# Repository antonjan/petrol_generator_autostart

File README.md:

# petrol_generator_autostart
This project is a remote controle generator start and stop system via Telegram web interface. It has 2 opto inputs 2  relay outputs and 2 servo Chocke controlerelay

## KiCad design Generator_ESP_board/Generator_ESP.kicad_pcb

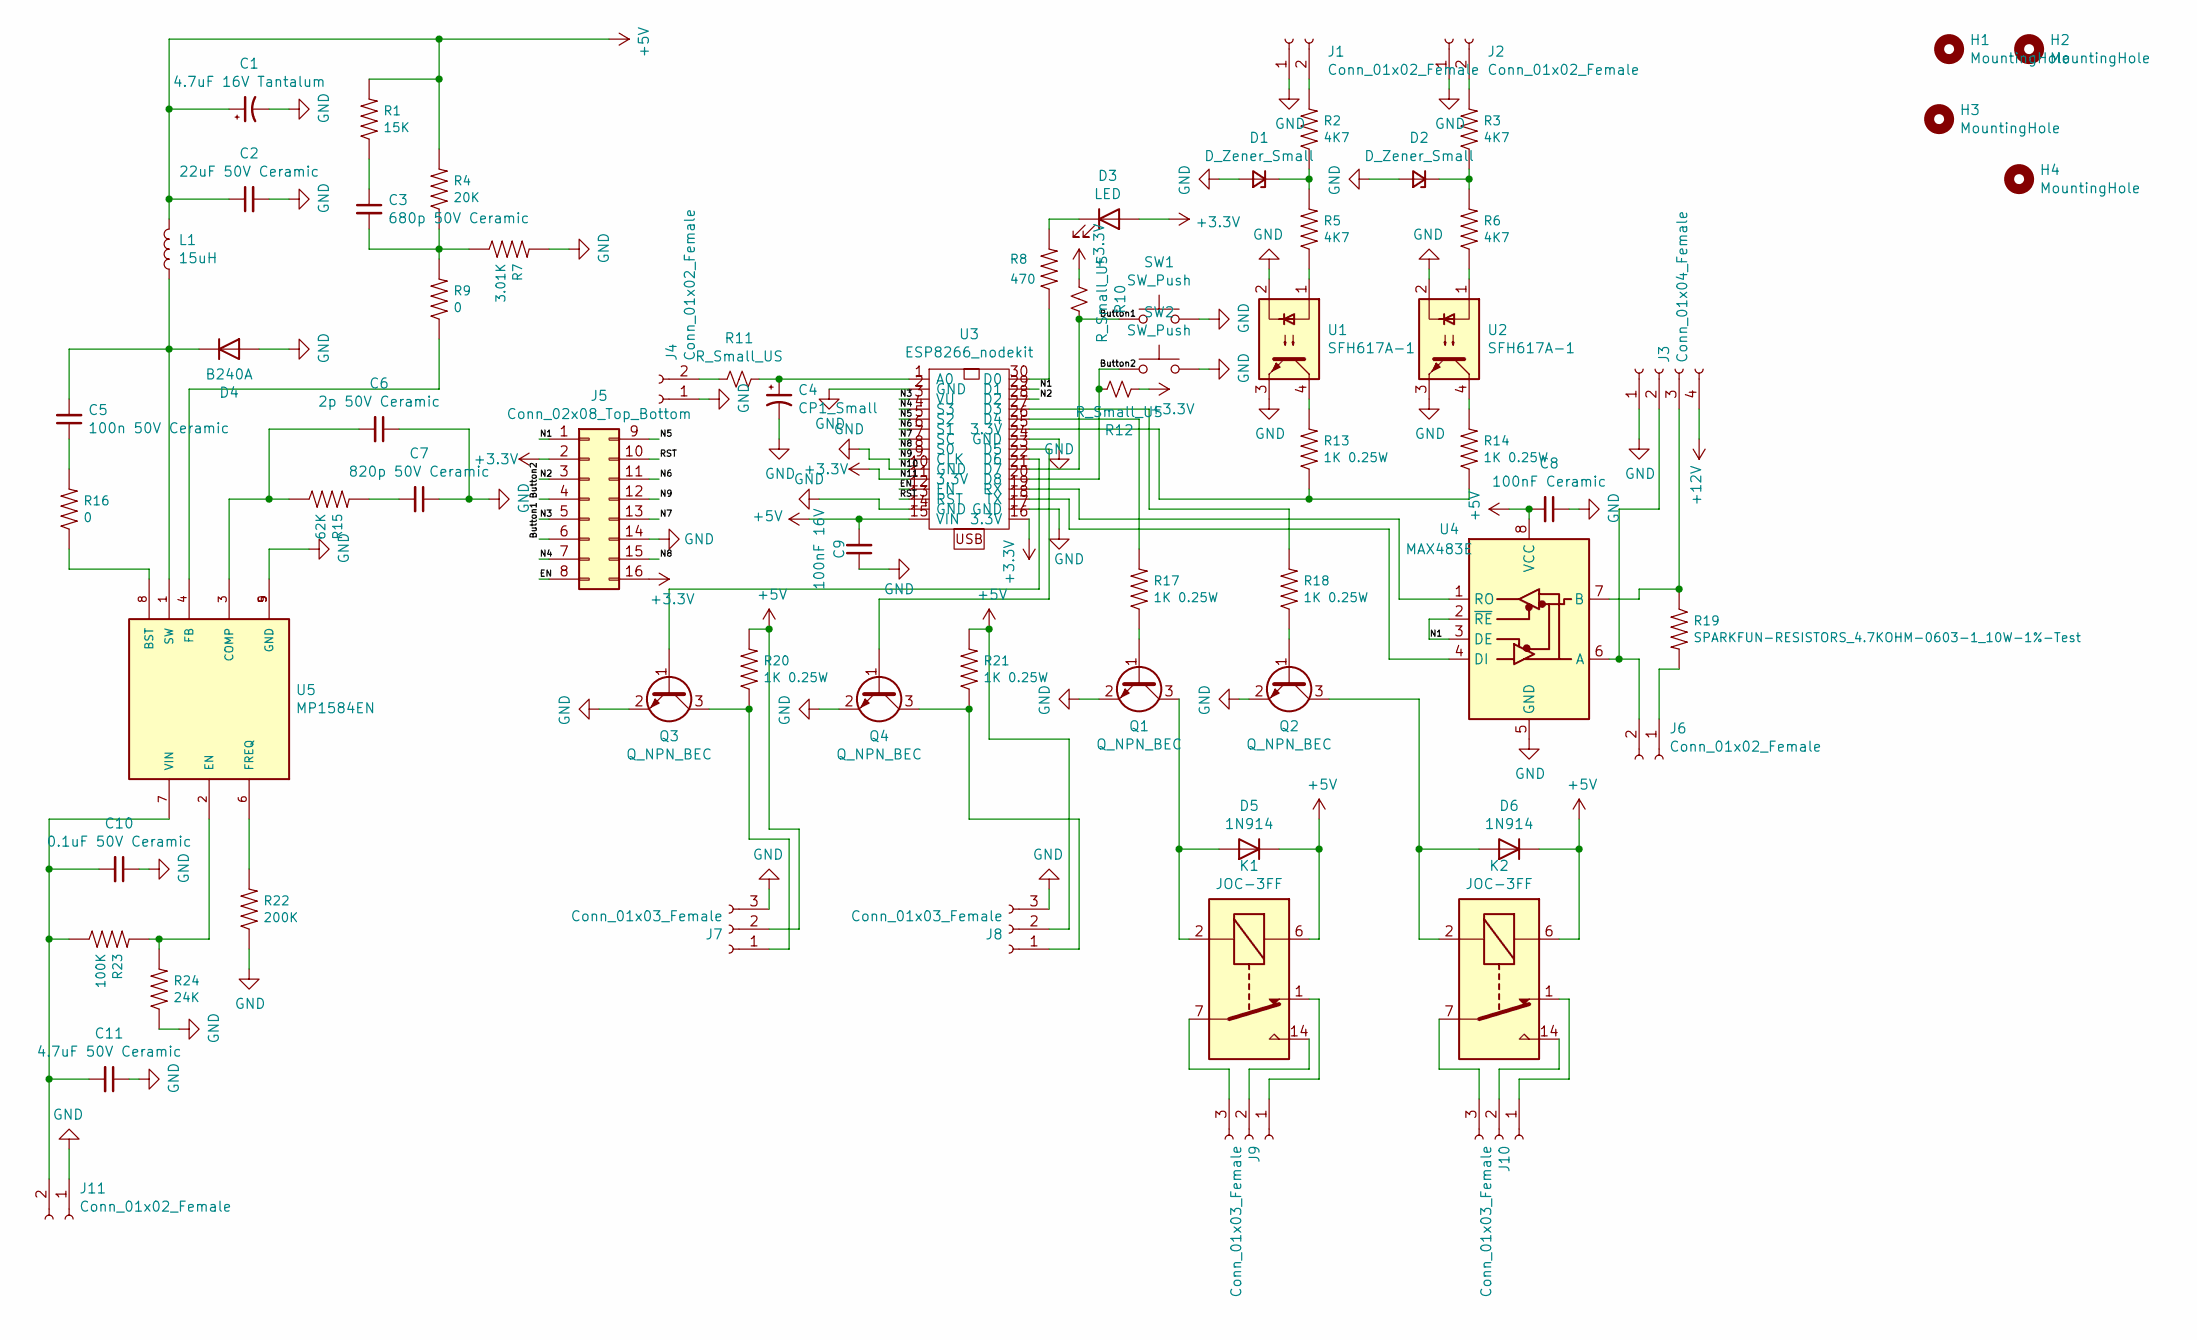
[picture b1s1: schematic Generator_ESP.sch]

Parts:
C1: 4.7uF 16V Tantalum; C_0805_2012Metric
C2: 22uF 50V Ceramic; C_2220_5650Metric
C3: 680p 50V Ceramic; C_0805_2012Metric
C4: CP1_Small; C_0805_2012Metric
C5: 100n 50V Ceramic; C_0805_2012Metric
C6: 2p 50V Ceramic; C_0805_2012Metric
C7: 820p 50V Ceramic; C_0805_2012Metric
C8: 100nF Ceramic; C_0805_2012Metric
C9: 100nF 16V; C_0805_2012Metric
C10: 0.1uF 50V Ceramic; C_0805_2012Metric
C11: 4.7uF 50V Ceramic; C_1206_3216Metric
D1, D2: D_Zener_Small; D_MELF
D3: LED; LED_D3.0mm
D4: B240A; D_SMA
D5, D6: 1N914; D_0805_2012Metric
H1, H2, H3, H4: MountingHole; MountingHole_3.2mm_M3
J1, J2, J11: Conn_01x02_Female; PhoenixContact_MCV_1,5_2-G-5.08_1x02_P5.08mm_Vertical
J3: Conn_01x04_Female; PhoenixContact_MCV_1,5_4-G-5.08_1x04_P5.08mm_Vertical
J4, J6: Conn_01x02_Female; PinHeader_1x02_P2.54mm_Vertical
J5: Conn_02x08_Top_Bottom; PinHeader_2x08_P2.54mm_Vertical
J7, J8, J9, J10: Conn_01x03_Female; PhoenixContact_MCV_1,5_3-G-5.08_1x03_P5.08mm_Vertical
K1, K2: JOC-3FF; Relay_SPDT_Finder_36.11
L1: 15uH; L_12x12mm_H4.5mm
Q1, Q2, Q3, Q4: Q_NPN_BEC; SOT-23
R1: 15K; R_0805_2012Metric_Pad1.20x1.40mm_HandSolder
R2, R3, R5, R6: 4K7; R_0805_2012Metric_Pad1.20x1.40mm_HandSolder
R4: 20K; R_0805_2012Metric_Pad1.20x1.40mm_HandSolder
R7: 3.01K; R_0805_2012Metric_Pad1.20x1.40mm_HandSolder
R8: 470; R_0805_2012Metric_Pad1.20x1.40mm_HandSolder
R9, R16: 0; R_0805_2012Metric_Pad1.20x1.40mm_HandSolder
R10, R11, R12: R_Small_US; R_0805_2012Metric_Pad1.20x1.40mm_HandSolder
R13, R14, R17, R18, R20, R21: 1K 0.25W; R_0805_2012Metric_Pad1.20x1.40mm_HandSolder
R15: 62K; R_0805_2012Metric_Pad1.20x1.40mm_HandSolder
R19: SPARKFUN-RESISTORS_4.7KOHM-0603-1_10W-1%-Test; R_0805_2012Metric_Pad1.20x1.40mm_HandSolder
R22: 200K; R_0805_2012Metric_Pad1.20x1.40mm_HandSolder
R23: 100K; R_0805_2012Metric_Pad1.20x1.40mm_HandSolder
R24: 24K; R_0805_2012Metric_Pad1.20x1.40mm_HandSolder
SW1, SW2: SW_Push; SW_SPST_B3U-1000P
U1, U2: SFH617A-1; SMDIP-4_W7.62mm
U3: ESP8266_nodekit; SEEED_113990105
U4: MAX483E; SOIC127P600X175-8N
U5: MP1584EN; SOIC127P600X170-9N

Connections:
+3V3: D3.2 (A), J5.2, J5.16, R10.2, R12.2, U3.11 (3.3V), U3.16 (3.3V)
+5V: C1.1, C2.1, C8.2, C9.2, D5.1 (K), D6.1 (K), J7.2, J8.2, K1.6, K2.6, L1.2, R1.2, R4.2, R20.2, R21.2, U3.15 (VIN), U4.8 (VCC)
+12V: J3.4
/Button1: J5.6, R10.1, SW1.1, U3.21 (D7)
/Button2: J5.4, R12.1, SW2.1, U3.20 (D8)
/EN: J5.8, U3.12 (EN)
/N1: J5.1, U3.29 (D1), U4.2 (~RE), U4.3 (DE)
/N2: J5.3, U3.28 (D2)
/N3: J5.5, U3.3 (VU)
/N4: J5.7, U3.4 (S3)
/N5: J5.9, U3.5 (S2)
/N6: J5.11, U3.6 (S1)
/N7: J5.13, U3.7 (SC)
/N8: J5.15, U3.8 (S0)
/N9: J5.12, U3.9 (CLK)
/RST: J5.10, U3.13 (RST)
GND: C1.2, C2.2, C4.2, C6.1, C7.1, C8.1, C9.1, C10.1, C11.1, D1.2 (A), D2.2 (A), D4.2 (A), J1.1, J2.1, J3.1, J4.1, J5.14, J7.3, J8.3, J11.1, Q1.2 (E), Q2.2 (E), Q3.2 (E), Q4.2 (E), R7.2, R22.1, R24.1, SW1.2, SW2.2, U1.2, U1.3, U2.2, U2.3, U3.2 (GND), U3.10 (GND), U3.14 (GND), U3.17 (GND), U3.24 (GND), U4.5 (GND), U5.5 (GND), U5.9 (GND)
unnamed: C3.1, R1.1
unnamed: C3.2, R4.1, R7.1, R9.2
unnamed: C4.1, R11.1, U3.1 (A0)
unnamed: C5.1, R16.2
unnamed: C5.2, D4.1 (K), L1.1, U5.1 (SW)
unnamed: C6.2, R15.1, U5.3 (COMP)
unnamed: C7.2, R15.2
unnamed: C10.2, C11.2, J11.2, R23.1, U5.7 (VIN)
unnamed: D1.1 (K), R2.1, R5.2
unnamed: D2.1 (K), R3.1, R6.2
unnamed: D3.1 (K), R8.2
unnamed: D5.2 (A), K1.2, Q1.3 (C)
unnamed: D6.2 (A), K2.2, Q2.3 (C)
unnamed: J1.2, R2.2
unnamed: J2.2, R3.2
unnamed: J3.2, J6.2, U4.6 (A)
unnamed: J3.3, R19.1, U4.7 (B)
unnamed: J4.2, R11.2
unnamed: J6.1, R19.2
unnamed: J7.1, Q3.3 (C), R20.1
unnamed: J8.1, Q4.3 (C), R21.1
unnamed: J9.1, K1.1
unnamed: J9.2, K1.14
unnamed: J9.3, K1.7, K1.8
unnamed: J10.1, K2.1
unnamed: J10.2, K2.14
unnamed: J10.3, K2.7, K2.8
unnamed: Q1.1 (B), R17.1
unnamed: Q2.1 (B), R18.1
unnamed: Q3.1 (B), U3.22 (D6)
unnamed: Q4.1 (B), U3.23 (D5)
unnamed: R5.1, U1.1
unnamed: R6.1, U2.1
unnamed: R8.1, U3.30 (D0)
unnamed: R9.1, U5.4 (FB)
unnamed: R13.1, R14.1, U3.25 (3.3V)
unnamed: R13.2, U1.4
unnamed: R14.2, U2.4
unnamed: R16.1, U5.8 (BST)
unnamed: R17.2, U3.26 (D4)
unnamed: R18.2, U3.27 (D3)
unnamed: R22.2, U5.6 (FREQ)
unnamed: R23.2, R24.2, U5.2 (EN)
unnamed: U3.18 (TX), U4.4 (DI)
unnamed: U3.19 (RX), U4.1 (RO)

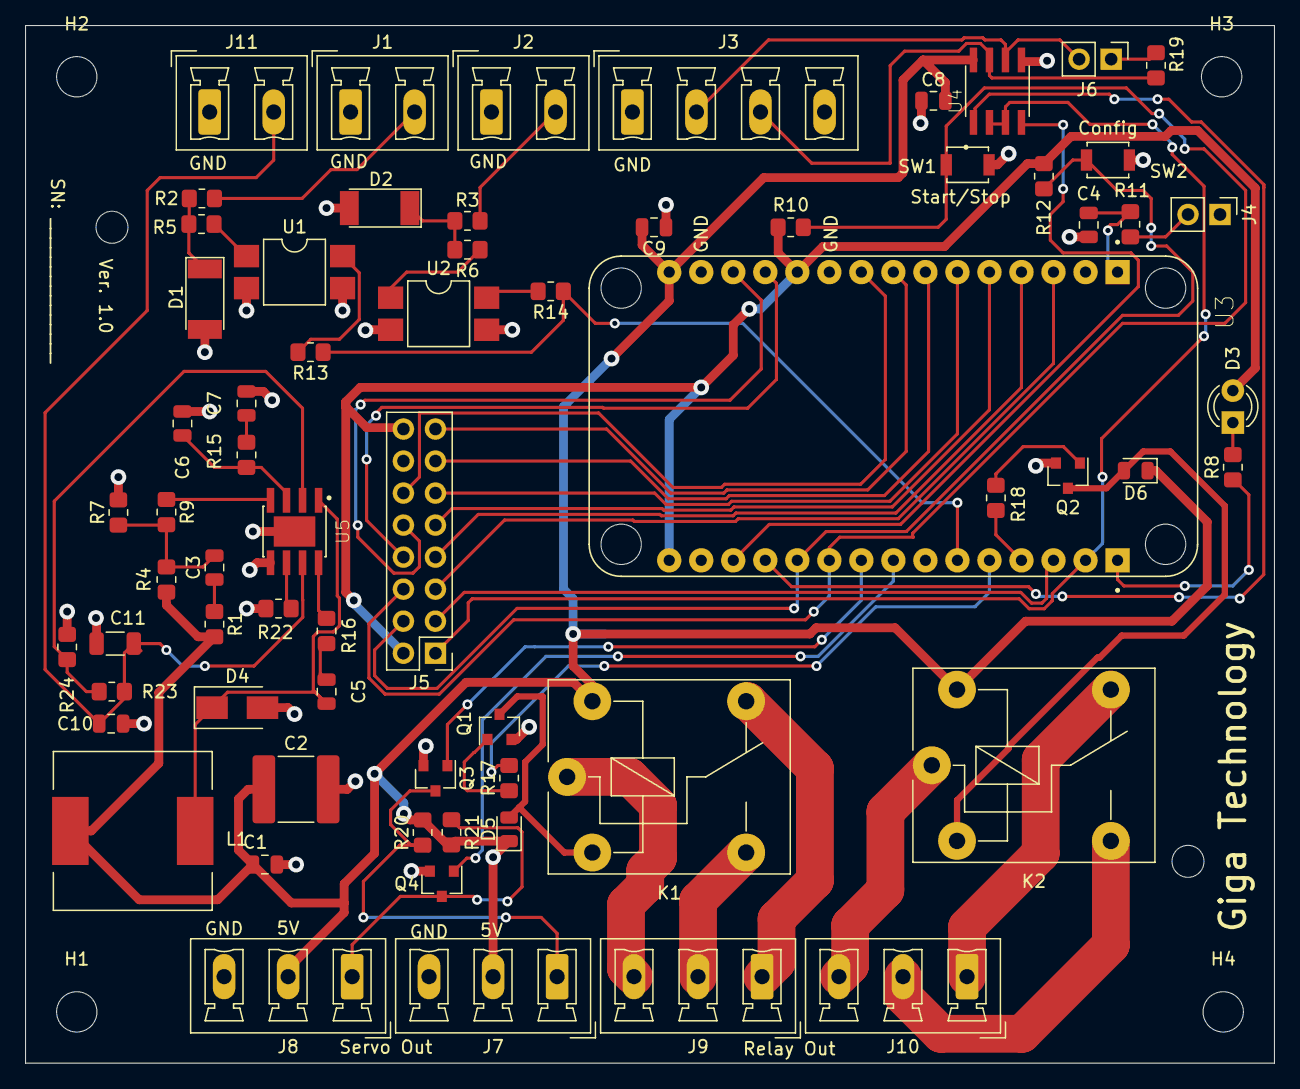
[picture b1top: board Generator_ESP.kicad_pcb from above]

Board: 2 copper layers, 99.1 x 82.3 mm, 70 parts (0 on the bottom side), 61 nets.

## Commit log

2021-01-25 first load of code
2022-01-12 adding latest pcb files
